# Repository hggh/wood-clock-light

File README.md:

# wood clock with ESP32

a rainbow wood clock with a custom LED matrix with 95 PL9823-F8 RBG LEDs.

 * ESP32
 * 85x pl9823-f8

### rainbow mode

### single color mode controllable via web

### simple web interface

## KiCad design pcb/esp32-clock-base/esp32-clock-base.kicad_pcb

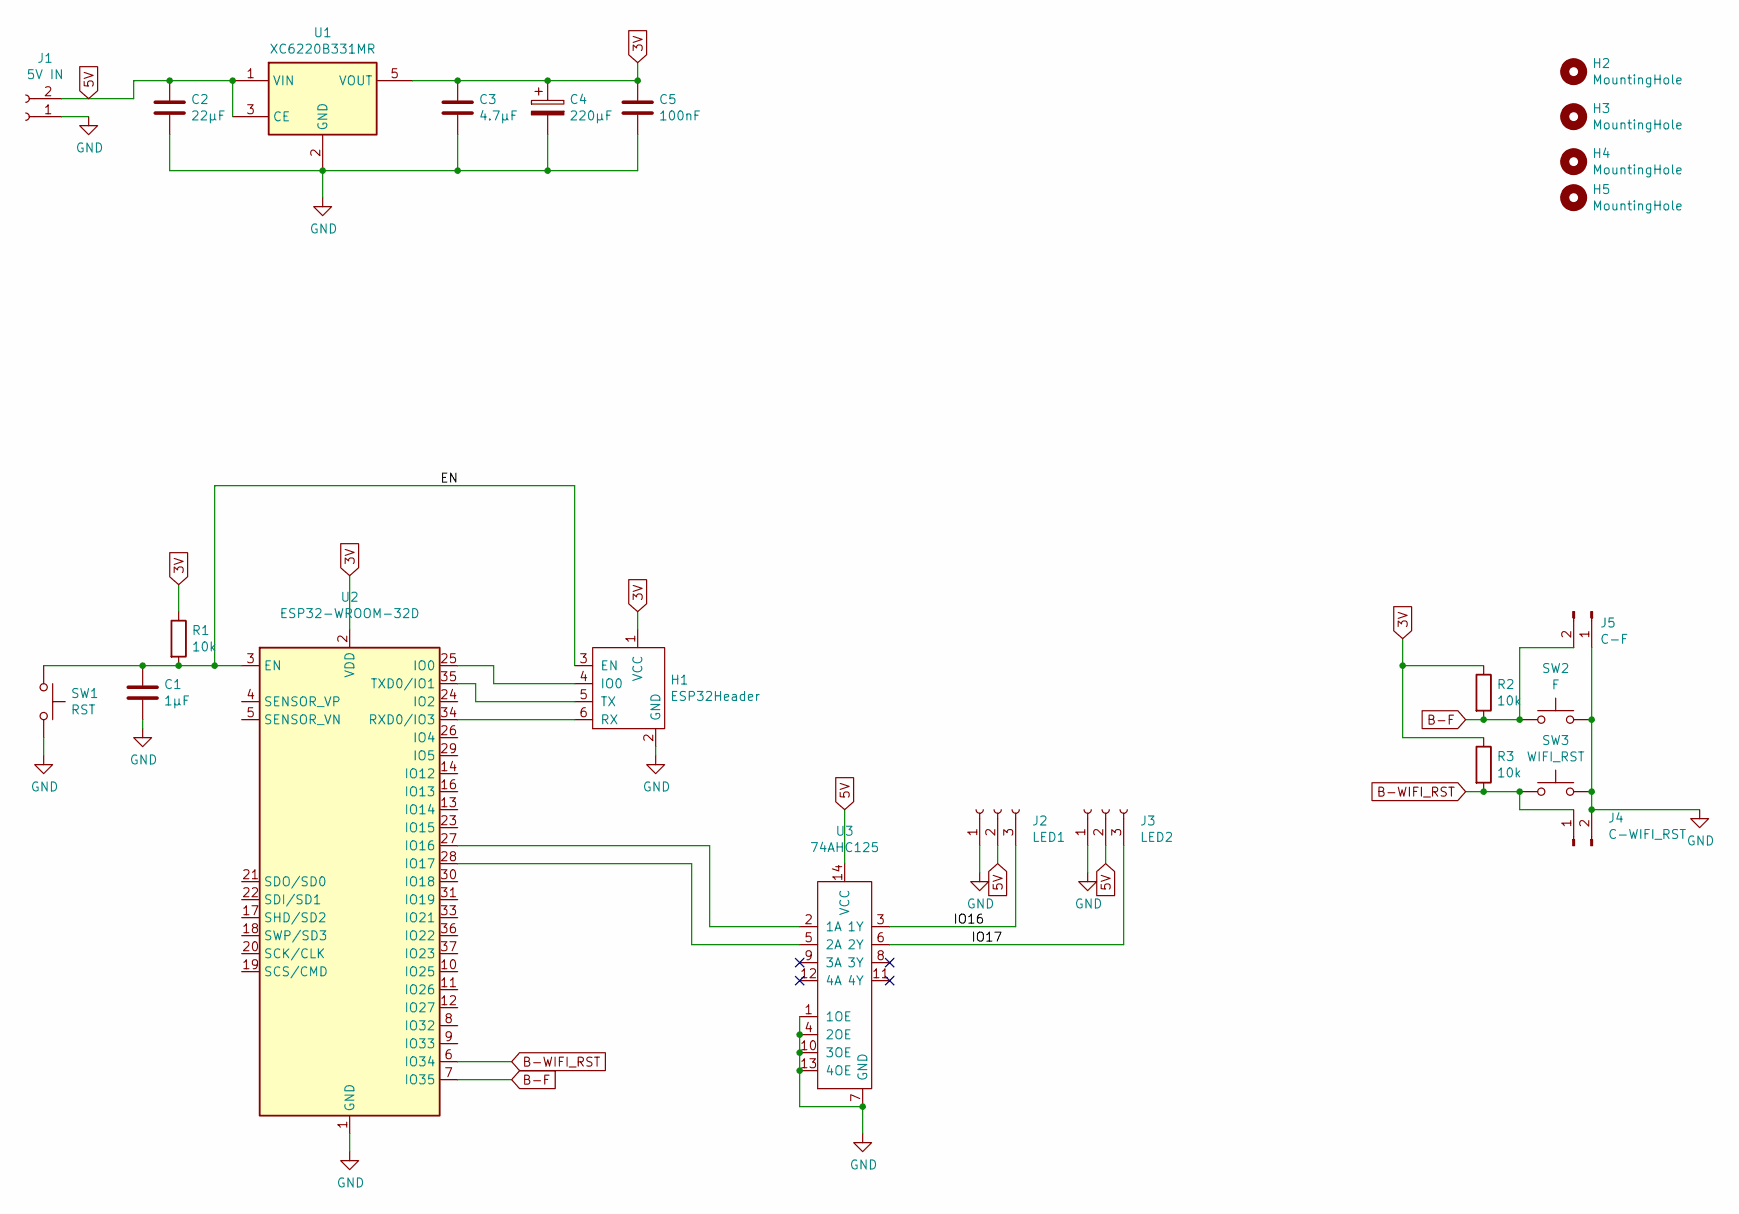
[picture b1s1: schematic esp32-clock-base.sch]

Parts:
C1: 1µF; C_0805_2012Metric
C2: 22µF; C_0805_2012Metric
C3: 4.7µF; C_0805_2012Metric
C4: 220µF; CP_EIA-7343-31_Kemet-D
C5: 100nF; C_0805_2012Metric
H1: ESP32Header; esp32-prog-header
H2, H3, H4, H5: MountingHole; MountingHole_3.2mm_M3
J1: 5V IN; PinHeader_1x02_P2.54mm_Vertical
J2: LED1; PinHeader_1x03_P2.54mm_Horizontal
J3: LED2; PinHeader_1x03_P2.54mm_Horizontal
J4: C-WIFI_RST; PinHeader_1x02_P2.00mm_Vertical
J5: C-F; PinHeader_1x02_P2.00mm_Vertical
R1, R2, R3: 10k; R_0805_2012Metric
SW1: RST; SMD_Button
SW2: F; SMD_Button
SW3: WIFI_RST; SMD_Button
U1: XC6220B331MR; SOT-23-5
U2: ESP32-WROOM-32D; ESP32-WROOM-32
U3: 74AHC125; SO-14_3.9x8.65mm_P1.27mm

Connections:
3V: C3.1, C4.1, C5.1, H1.1 (VCC), R1.1, R2.1, R3.1, U1.5 (VOUT), U2.2 (VDD)
5V: C2.1, J1.2, J2.2, J3.2, U1.1 (VIN), U1.3 (CE), U3.14 (VCC)
/EN: C1.1, H1.3 (EN), R1.2, SW1.1, U2.3 (EN)
/IO16: J2.3, U3.3 (1Y)
/IO17: J3.3, U3.6 (2Y)
B-F: J5.2, R2.2, SW2.1, U2.7 (IO35)
B-WIFI_RST: J4.1, R3.2, SW3.1, U2.6 (IO34)
GND: C1.2, C2.2, C3.2, C4.2, C5.2, H1.2 (GND), J1.1, J2.1, J3.1, J4.2, J5.1, SW1.2, SW2.2, SW3.2, U1.2 (GND), U2.1 (GND), U2.15 (GND), U2.38 (GND), U2.39 (GND), U3.1 (1OE), U3.4 (2OE), U3.7 (GND), U3.10 (3OE), U3.13 (4OE)
unnamed: H1.4 (IO0), U2.25 (IO0)
unnamed: H1.5 (TX), U2.35 (TXD0/IO1)
unnamed: H1.6 (RX), U2.34 (RXD0/IO3)
unnamed: U2.27 (IO16), U3.2 (1A)
unnamed: U2.28 (IO17), U3.5 (2A)

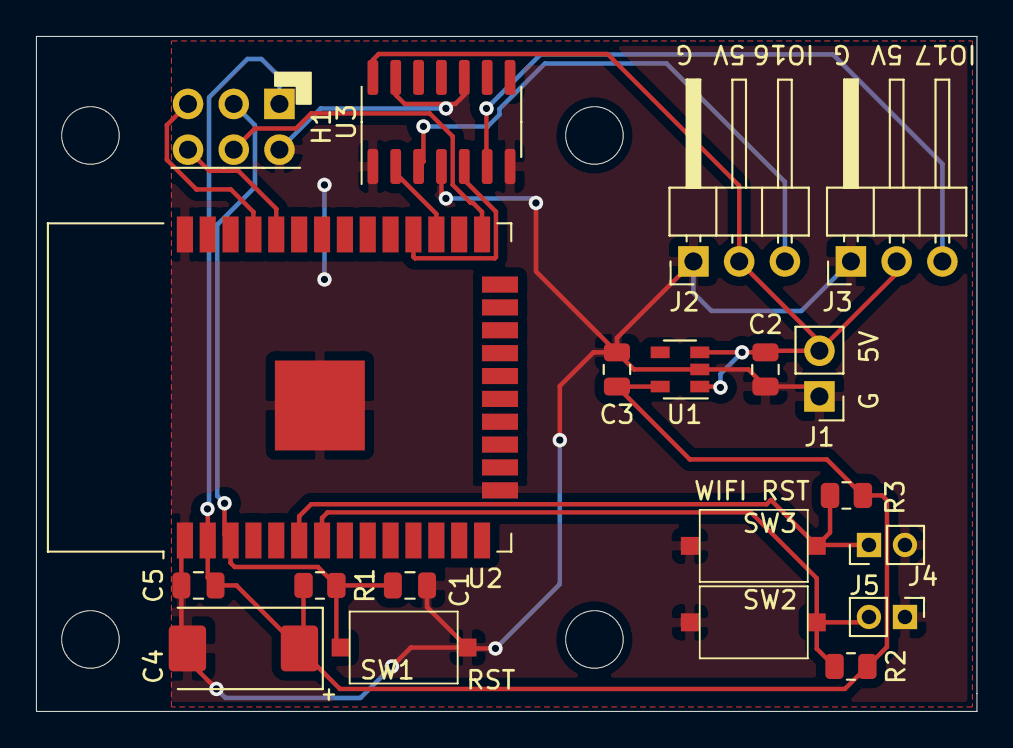
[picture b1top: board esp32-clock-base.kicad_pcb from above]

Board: 2 copper layers, 52.2 x 37.5 mm, 24 parts (0 on the bottom side), 13 nets.

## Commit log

2017-07-28 initial wood clock
2017-07-28 added readme
2017-07-28 added pics
2017-07-28 removed notify about missing ds1307
2021-02-28 update to esp32
2021-02-28 add opfer LED; add brightness control to webserver
2021-02-28 add pics
2021-02-28 add webinterface
2021-03-07 update html with current settings
2021-03-15 set correct Europe/Berlin timezone
2021-04-29 add ESP32 base pcb
2021-05-06 update to new PCB with 74AHC125
2021-05-14 IO34 has no pullup
2021-11-16 change to iotadmin
